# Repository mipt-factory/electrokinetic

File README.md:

# electrokinetic

Электромеханическая интерактивная модель котика.

Видео о процессе создания.
https://youtu.be/Dcu6bxMXSuQ

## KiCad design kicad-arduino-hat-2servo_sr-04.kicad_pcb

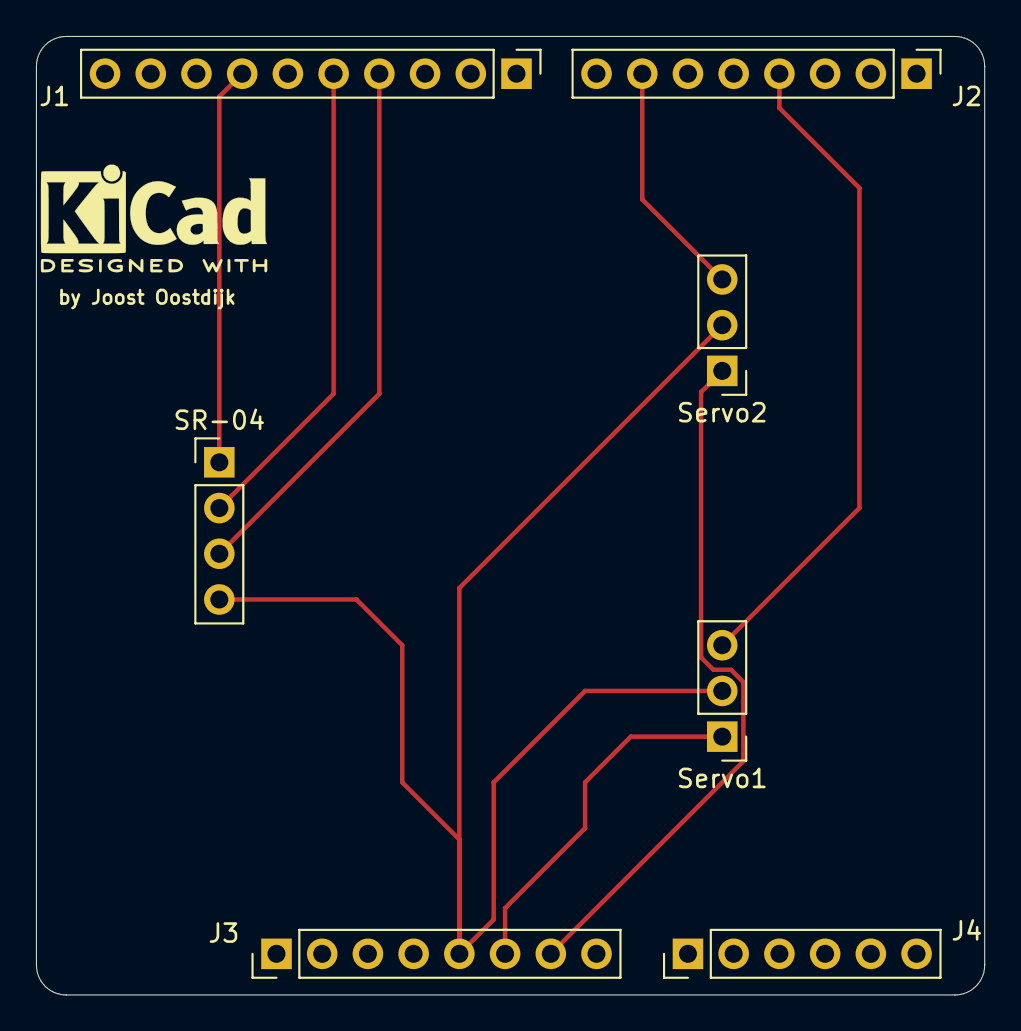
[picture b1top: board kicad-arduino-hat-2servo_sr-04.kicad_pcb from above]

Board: 2 copper layers, 52.7 x 53.3 mm, 7 parts (0 on the bottom side), 6 nets.

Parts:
J1: Digital; PinHeader_1x10_P2.54mm_Vertical
J2: Digital; PinHeader_1x08_P2.54mm_Vertical
J3: POWER; PinHeader_1x08_P2.54mm_Vertical
J4: Analog IN; PinHeader_1x06_P2.54mm_Vertical
SR-04: PinHeader_1x04_P2.54mm_Vertical
Servo1, Servo2: PinHeader_1x03_P2.54mm_Vertical

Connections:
/arduino-uno-connectors/3(PWM): J2.4, Servo1.3
/arduino-uno-connectors/5V: J3.5, SR-04.4, Servo1.2, Servo2.2
/arduino-uno-connectors/6(PWM): J2.7, Servo2.3
/arduino-uno-connectors/11(PWM): J1.4, SR-04.3
/arduino-uno-connectors/12: J1.5, SR-04.2
/arduino-uno-connectors/GND: J1.7, J3.6, J3.7, SR-04.1, Servo1.1, Servo2.1

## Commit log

2023-04-27 init commit
